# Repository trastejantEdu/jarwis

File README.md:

## ¿Qué es Jarwis?
Jarwis es la versión simplificada basada en web del sistema domotico de control JARVIS https://github.com/makespacemadrid/Jarvis

Basado en los modulos de bajo coste NodeMCU y controlado desde una Raspberry Pi que se encarga del automatismo y control de todos los módulo. La comunicación se establece por WiFi y un sistema basado en comunicaciones WEB permite monitorizar distintos parametros tales como:

⋅⋅* Humedad
⋅⋅* Temperatura
⋅⋅* Luz

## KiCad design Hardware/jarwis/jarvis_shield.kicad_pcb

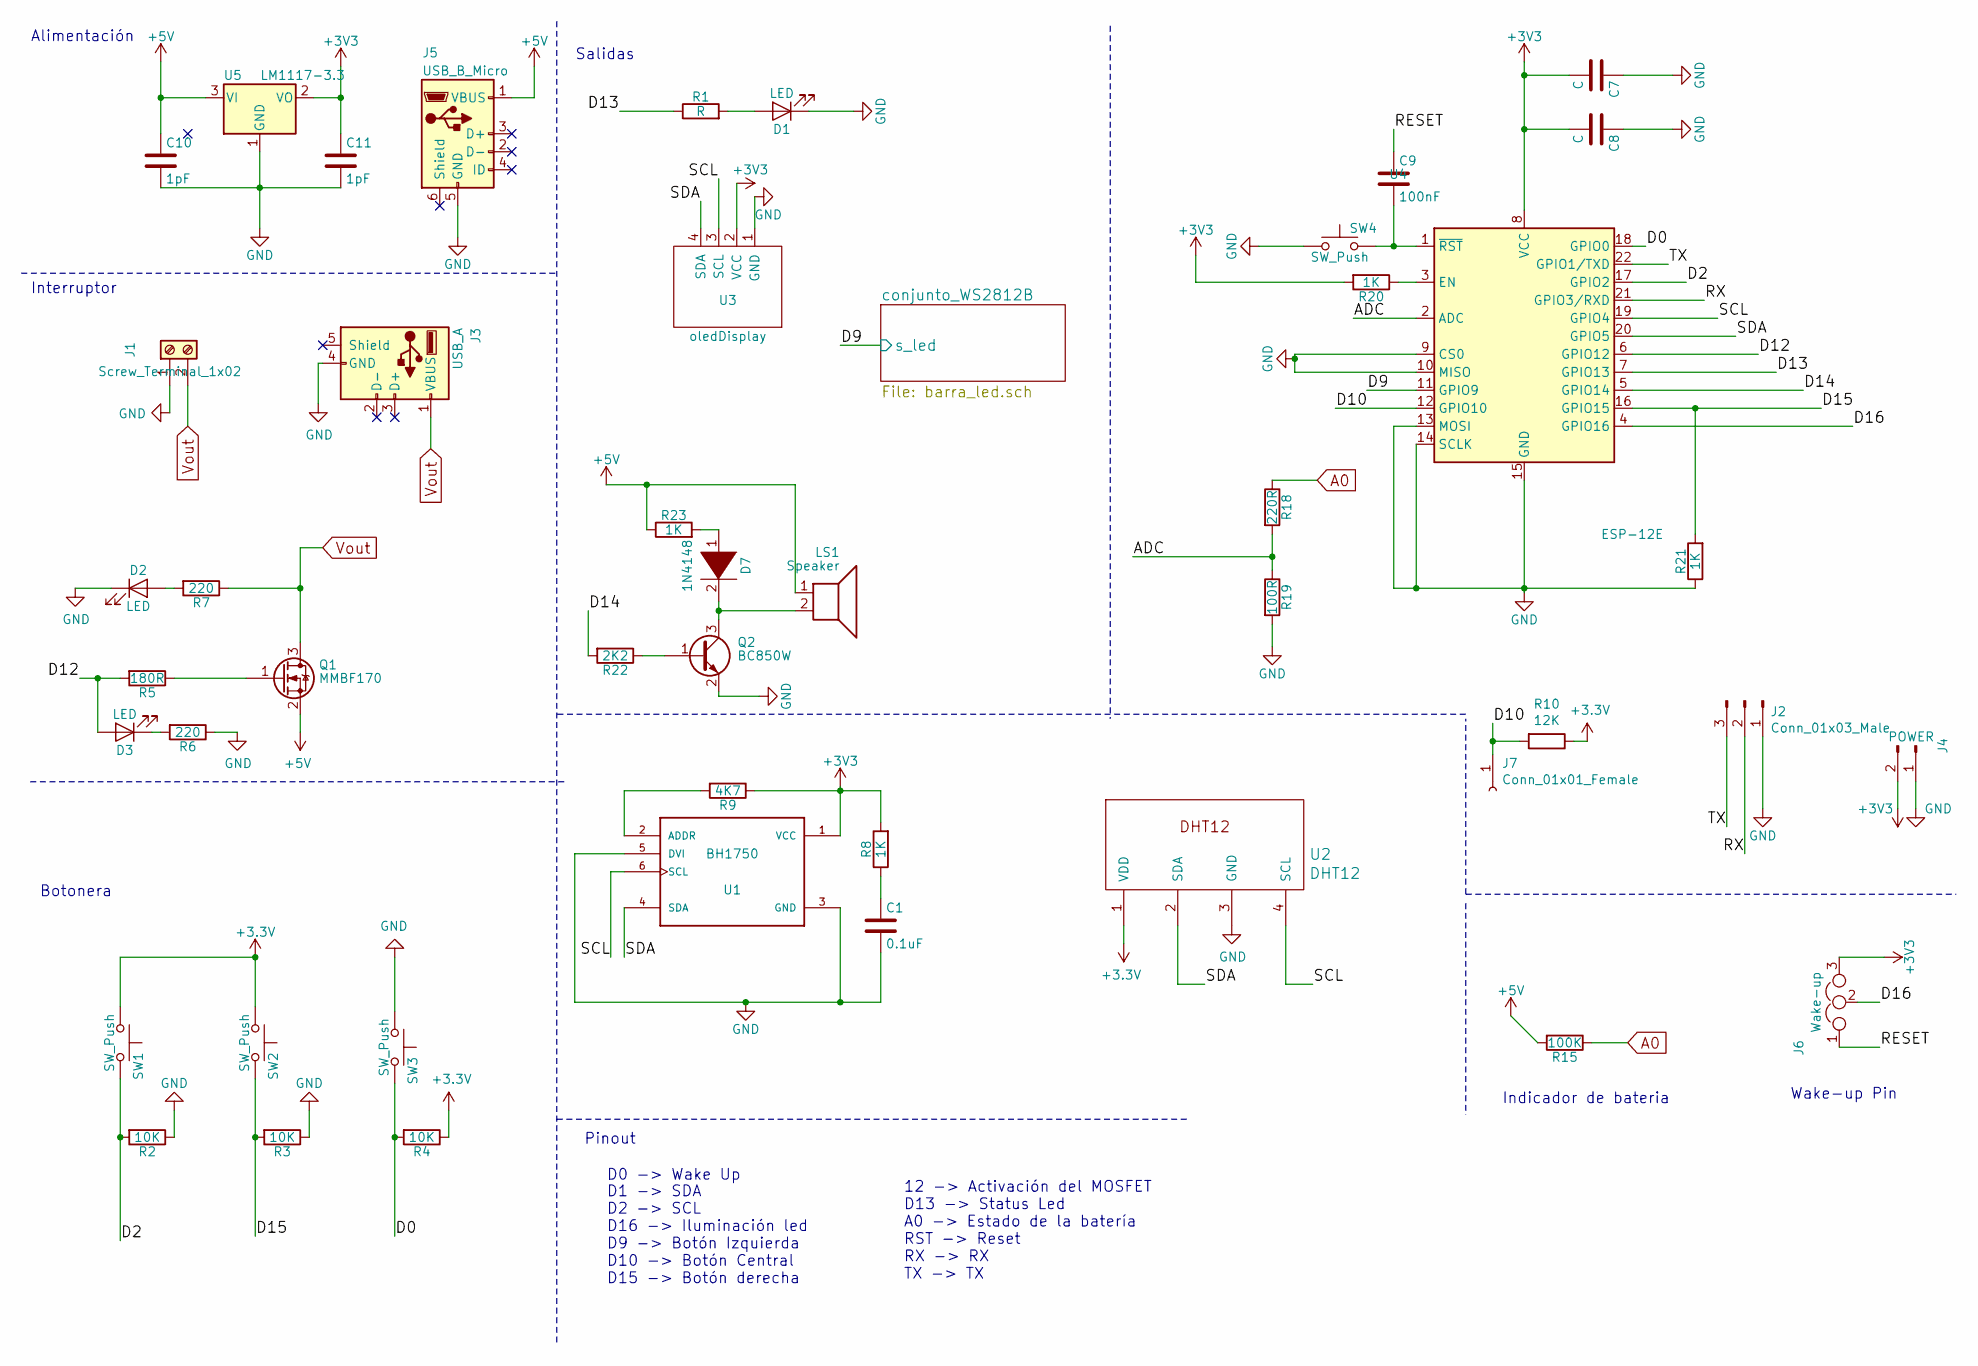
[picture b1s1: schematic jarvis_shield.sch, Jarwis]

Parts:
C1: 0.1uF; C_0805_2012Metric_Pad1.15x1.40mm_HandSolder
C7, C8: C; C_0805_2012Metric_Pad1.15x1.40mm_HandSolder
C9: 100nF; C_0805_2012Metric_Pad1.15x1.40mm_HandSolder
C10, C11: 1pF; C_0805_2012Metric_Pad1.15x1.40mm_HandSolder
D1, D2, D3: LED; LED_0805_2012Metric_Pad1.15x1.40mm_HandSolder
D7: 1N4148; D_0805_2012Metric_Pad1.15x1.40mm_HandSolder
J1: Screw_Terminal_1x02; TerminalBlock_bornier-2_P5.08mm
J2: Conn_01x03_Male; PinHeader_1x03_P2.54mm_Vertical
J3: USB_A; USB_B_OST_USB-B1HSxx_Horizontal
J4: POWER; PinHeader_1x02_P2.54mm_Vertical
J5: USB_B_Micro; USB_Micro-B_Wuerth_629105150521_CircularHoles
J6: Wake-up; PinHeader_1x02_P2.54mm_Vertical
J7: Conn_01x01_Female; PinHeader_1x01_P2.54mm_Vertical
LS1: Speaker; MagneticBuzzer_Kingstate_KCG0601
Q1: MMBF170; SOT-23-5_HandSoldering
Q2: BC850W; SOT-323_SC-70; Mouser REF 621-MMBT4401-13-F
R1: R; R_0805_2012Metric_Pad1.15x1.40mm_HandSolder
R2: 10K; R_0805_2012Metric_Pad1.15x1.40mm_HandSolder; Mouser REF 754-RS2012P-103-DT53
R3, R4: 10K; R_0805_2012Metric_Pad1.15x1.40mm_HandSolder
R5: 180R; R_0805_2012Metric_Pad1.15x1.40mm_HandSolder
R6, R7: 220; R_0805_2012Metric_Pad1.15x1.40mm_HandSolder
R8, R20, R21, R23: 1K; R_0805_2012Metric_Pad1.15x1.40mm_HandSolder
R9: 4K7; R_0805_2012Metric_Pad1.15x1.40mm_HandSolder
R10: 12K; R_0805_2012Metric_Pad1.15x1.40mm_HandSolder
R15: 100K; R_0805_2012Metric_Pad1.15x1.40mm_HandSolder
R18: 220R; R_0805_2012Metric_Pad1.15x1.40mm_HandSolder
R19: 100R; R_0805_2012Metric_Pad1.15x1.40mm_HandSolder
R22: 2K2; R_0805_2012Metric_Pad1.15x1.40mm_HandSolder
SW1, SW2, SW3: SW_Push; SW_PUSH_6mm
SW4: SW_Push; SW_Tactile_SPST_Angled_PTS645Vx31-2LFS
U1: BH1750; SOTFL50P300X75-6N; MOUSER REF 755-BH1750FVI-TR
U2: DHT12
U3: oledDisplay; oled_display_0.96
U4: ESP-12E
U5: LM1117-3.3; SOT-223-3_TabPin2

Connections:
+5V: C10.1, J5.1 (VBUS), LS1.1, Q1.2 (S), R15.2, R23.1, U5.3 (VI); also elsewhere on the board
/ADC: R18.2, R19.1, U4.2 (ADC)
/D0: R4.2, SW3.2, U4.18 (GPIO0)
/D2: R2.2, SW1.2, U4.17 (GPIO2)
/D9: U4.11 (GPIO9); also elsewhere on the board
/D10: J7.1, R10.2, U4.12 (GPIO10)
/D12: D3.2 (A), R5.2, U4.6 (GPIO12)
/D13: R1.1, U4.7 (GPIO13)
/D14: R22.2, U4.5 (GPIO14)
/D15: R3.2, R21.2, SW2.2, U4.16 (GPIO15)
/D16: J6.2, U4.4 (GPIO16)
/RESET: C9.1, J6.1
/RX: J2.2, U4.21 (GPIO3/RXD)
/SCL: U1.6 (SCL), U2.4 (SCL), U3.3 (SCL), U4.19 (GPIO4)
/SDA: U1.4 (SDA), U2.2 (SDA), U3.4 (SDA), U4.20 (GPIO5)
/TX: J2.3, U4.22 (GPIO1/TXD)
A0: R15.1, R18.1
GND: C1.2, C7.1, C8.1, C10.2, C11.2, D1.1 (K), D2.1 (K), J1.1, J2.1, J3.4 (GND), J4.1, J5.5 (GND), Q2.2 (E), R2.1, R3.1, R6.1, R19.2, R21.1, SW3.1, SW4.1, U1.3 (GND), U1.5 (DVI), U2.3 (GND), U3.1 (GND), U4.9 (CS0), U4.10 (MISO), U4.13 (MOSI), U4.14 (SCLK), U4.15 (GND), U5.1 (GND); also elsewhere on the board
unnamed: C1.1, R8.1
unnamed: C9.2, SW4.2, U4.1 (~RST)
unnamed: D1.2 (A), R1.2
unnamed: D2.2 (A), R7.2
unnamed: D3.1 (K), R6.2
unnamed: D7.1 (K), R23.2
unnamed: D7.2 (A), LS1.2, Q2.3 (C)
unnamed: Q1.1 (G), R5.1
unnamed: Q2.1 (B), R22.1
unnamed: R9.2, U1.2 (ADDR)
unnamed: R20.1, U4.3 (EN)
Vout: J1.2, J3.1 (VBUS), Q1.3 (D), R7.1

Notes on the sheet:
Salidas
Interruptor
Botonera
Pinout
D1 -> SDA D2 -> SCL D16 -> Iluminación led D9 -> Botón Izquierda D10 -> Botón Central D15 -> Botón derecha
12 -> Activación del MOSFET D13 -> Status Led A0 -> Estado de la batería RST -> Reset RX -> RX TX -> TX
Indicador de bateria
D0 -> Wake Up
Wake-up Pin
Alimentación

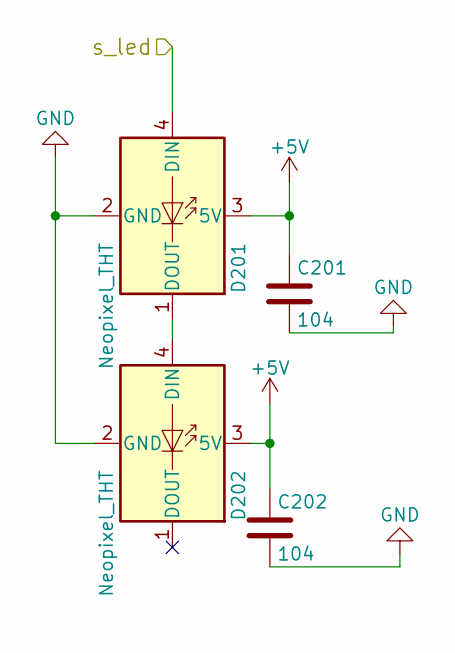
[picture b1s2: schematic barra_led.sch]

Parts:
C201, C202: 104; C_0805_2012Metric_Pad1.15x1.40mm_HandSolder
D201, D202: Neopixel_THT; LED_WS2812B_PLCC4_5.0x5.0mm_P3.2mm

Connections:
+5V: C201.1, C202.1, D201.3 (5V), D202.3 (5V); also elsewhere on the board
/D9: D201.4 (DIN); also elsewhere on the board
GND: C201.2, C202.2, D201.2 (GND), D202.2 (GND); also elsewhere on the board
unnamed: D201.1 (DOUT), D202.4 (DIN)

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
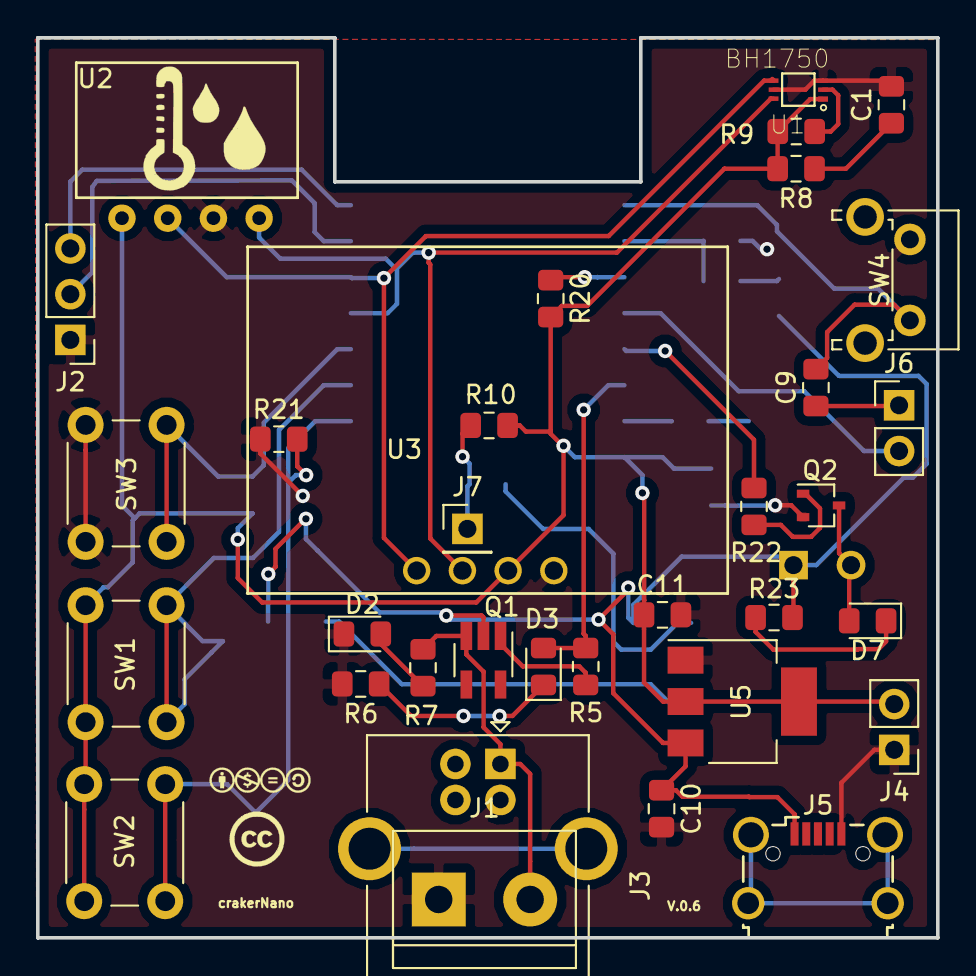
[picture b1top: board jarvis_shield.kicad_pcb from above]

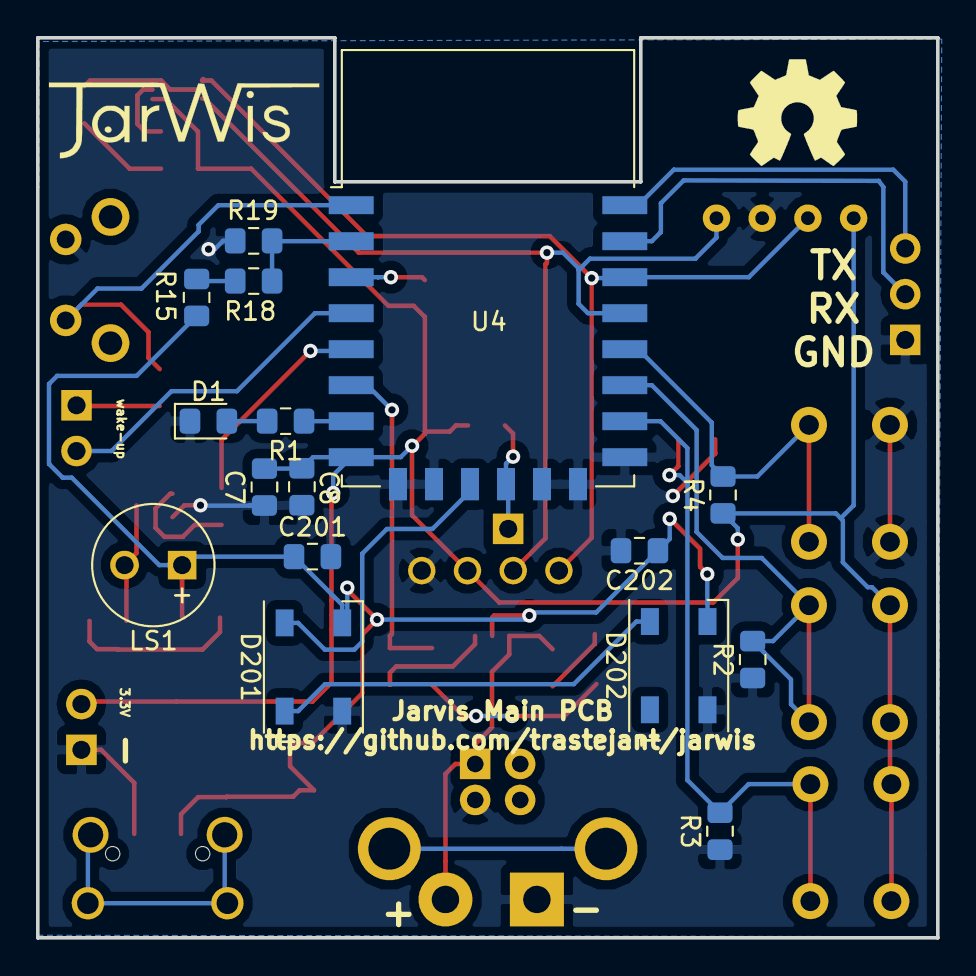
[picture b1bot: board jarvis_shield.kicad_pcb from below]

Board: 2 copper layers, 50.0 x 50.0 mm, 50 parts (16 on the bottom side), 32 nets.

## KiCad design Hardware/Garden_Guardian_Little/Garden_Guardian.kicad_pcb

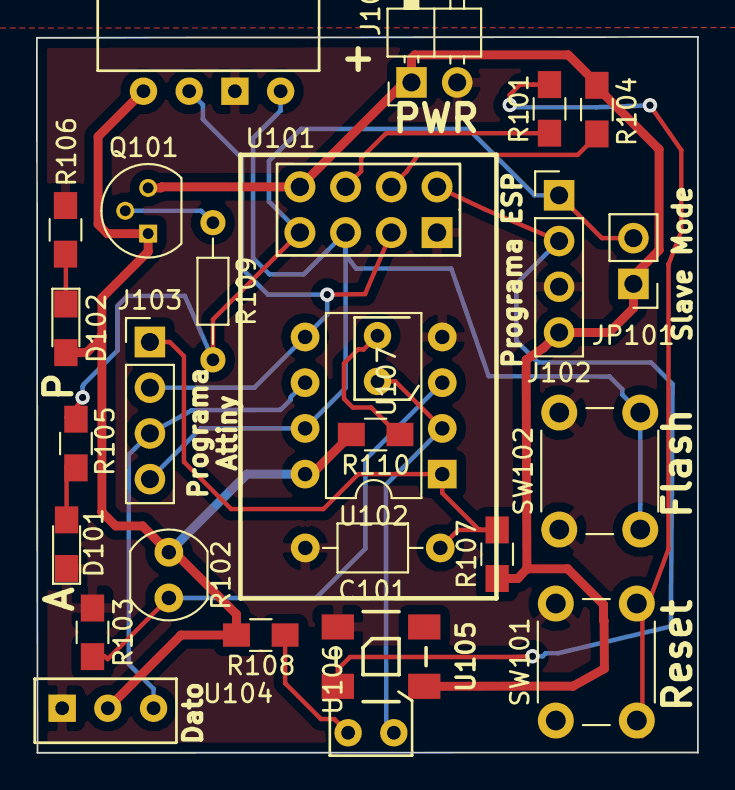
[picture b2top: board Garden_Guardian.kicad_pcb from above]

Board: 2 copper layers, 36.7 x 39.8 mm, 27 parts (0 on the bottom side), 19 nets.

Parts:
C101: C; C_Axial_L3.8mm_D2.6mm_P7.50mm_Horizontal
D101, D102: LED; LED_0805_HandSoldering
J101: Conn_01x02; Pin_Header_Angled_1x02_Pitch2.54mm
J102: PROGRAMA_ESP; Pin_Header_Straight_1x04_Pitch2.54mm
J103: PROGRAMA ATTINY; Pin_Header_Straight_1x04_Pitch2.54mm
JP101: No Slave Mode; Pin_Header_Straight_1x02_Pitch2.54mm
Q101: BS170; TO-92_Molded_Narrow
R101, R104: 10k; R_0805_HandSoldering
R102: LDR03; Resistor_LDR_4.9x4.2_RM2.54
R103: 10K; R_0805_HandSoldering
R105, R106: 56R; R_0805_HandSoldering
R107, R108, R110: R; R_0805_HandSoldering
R109: 330; R_Axial_DIN0204_L3.6mm_D1.6mm_P7.62mm_Horizontal
SW101: Reset; SW_PUSH_6mm_h7.3mm
SW102: FLASH; SW_PUSH_6mm_h7.3mm
U101: ESP-01v090; ESP-01
U102: ATTINY13-20PU; DIP-8_W7.62mm
U103: DHT12
U104: FS1000A; FS1000A_vertical
U105: WS2812B
U106, U107: sonda_humedad; externa

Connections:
/ACTIVADOR: J102.1, JP101.2, R105.2, R109.2, U101.4
/HUMEDAD: U102.2, U106.1, U107.1
/LDR: R102.2, R103.2, U102.3
/PWR_ON: D102.2, Q101.1, R102.1, R108.2, R110.2, U102.8, U103.1, U104.2
/RADIO: J103.3, U102.6, U104.1
/RST: C101.1, J103.1, R107.2, U102.1
/SCL: J103.4, SW102.2, U101.3, U102.7, U103.4
/SDA: J103.2, U101.2, U102.5, U103.2
/STATUS_LED: J102.2, U101.5, U105.4
GND: C101.2, D101.1, J101.2, J102.3, R103.1, R106.2, SW101.1, SW102.1, U101.1, U102.4, U103.3, U104.3, U105.3
unnamed: D101.2, R105.1
unnamed: D102.1, R106.1
unnamed: Q101.2, R109.1
unnamed: R101.1, U101.7
unnamed: R101.2, SW101.2
unnamed: R104.1, U101.6
unnamed: R108.1, U106.2
unnamed: R110.1, U107.2
VCC: J101.1, J102.4, JP101.1, Q101.3, R104.2, R107.1, U101.8, U105.1

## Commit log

2017-01-19 Versión basica funcional para registrar lecturas
2017-01-21 Carcasa para los modulos
2017-01-24 Servidor de registro y visualización básica de datos
2017-02-11 Incluida salida del USB para reprogramación y carga Rectificadas las tolerancias stl de la tapa
2017-04-16 - Implementado reloj - Pantalla de info del modulo - Pantalla de datos
2017-04-16 Modo reloj y mejoras en la visualización
    - Implementado reloj
    - Implementada librería NTP
    - Pantalla de información del modulo
    - Pantalla de datos
2017-06-02 configuracion de modulos subida de imagenes
2017-07-14 Implementada interfaz web y mejorada la visualización por pantalla.
2017-08-08 Modo grafico para la indicación de conectado/desconectado
2017-08-10 Implementado sistema de medición de señal
2017-08-12 Implementada comprobacion de sensores para evitar lecturas erroneas
2017-09-28 Nueva carcasa para modulo magnetico horizontal
2017-10-15 arreglado el merger
2017-11-03 Modulo Interruptor
2017-11-03 Carcasa para modulo en PCB y para modulo con protoboard
2017-11-03 Renombrado de carpetas Incluidos mini-modulos
2017-11-03 mejora de imagenes
2017-11-17 Incluidos menus
2017-12-10 Mejoras en la conexion y puesta en hora
2018-02-20 Correccion de la hora para horario de verano/invierno Mejora de la puesta en hora de los modulos Mejora de la subida de datos al servidor
2018-02-24 Logo Jarwis
2018-02-24 Mejorada la actualizacion del modulo externo
2018-02-24 Implementacion del sistema de bajo consumo en modulos externos
2018-07-07 Imagenes Mejora en la carcasa de los módulos 0.1
    9
2018-07-23 Esquema y PCB del módulo Jarwis VERSION PENDIENTE DE REVISION
2018-08-04 Primera version del sistema low cost de juidado del jardin
2018-09-07 Firmware para control de modulos sonoff Modulos de control de Jardin Version NO DEFINITIVA del modulo jarwis principal Modulos de control del nivel del agua del aire acondicionado
2018-09-08 Placa lista para fabricar
2018-10-27 Jarwis Garden Guardian listo para fabricar
    Ficheros de PCB del monitorizador de macetas y jardines para Jarwis
2018-10-27 Ficheros de la PCB del módulo Jarwis
